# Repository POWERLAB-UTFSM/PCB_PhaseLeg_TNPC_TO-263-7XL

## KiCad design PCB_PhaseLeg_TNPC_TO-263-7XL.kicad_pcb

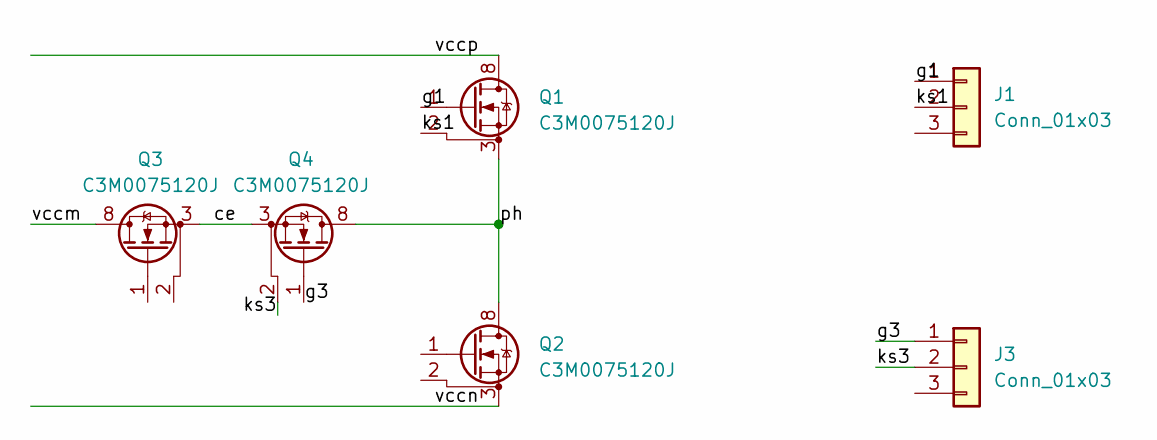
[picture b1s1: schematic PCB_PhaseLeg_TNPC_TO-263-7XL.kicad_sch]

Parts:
J1, J3: Conn_01x03; PinHeader_1x03_P1.27mm_Vertical_SMD_Pin1Left
Q1, Q2, Q3, Q4: C3M0075120J; TO-263-7_TabPin8

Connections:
/ce: Q3.3 (S), Q3.4 (S), Q3.5 (S), Q3.6 (S), Q3.7 (S), Q4.3 (S), Q4.4 (S), Q4.5 (S), Q4.6 (S), Q4.7 (S)
/g1: J1.1, Q1.1 (G)
/g3: J3.1, Q4.1 (G)
/ks1: J1.2, Q1.2 (DS)
/ks3: J3.2, Q4.2 (DS)
/ph: Q1.3 (S), Q1.4 (S), Q1.5 (S), Q1.6 (S), Q1.7 (S), Q2.8 (D), Q4.8 (D)
/vccm: Q3.8 (D)
/vccn: Q2.3 (S), Q2.4 (S), Q2.5 (S), Q2.6 (S), Q2.7 (S)
/vccp: Q1.8 (D)

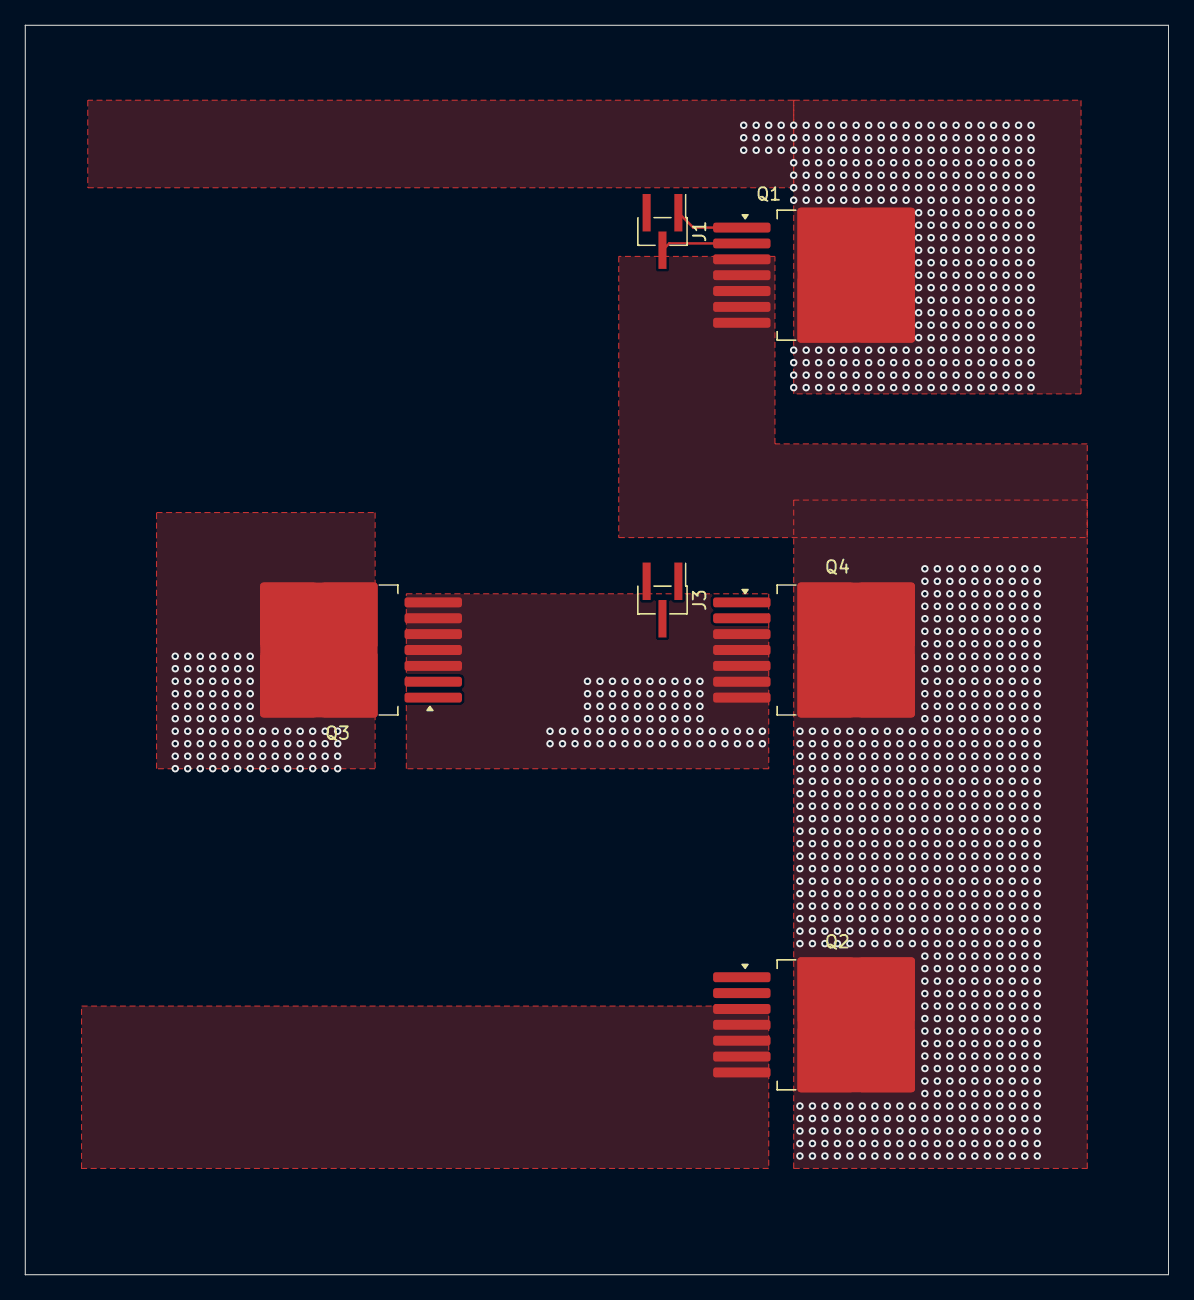
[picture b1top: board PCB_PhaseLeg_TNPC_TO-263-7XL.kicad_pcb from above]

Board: 2 copper layers, 91.5 x 100.0 mm, 6 parts (0 on the bottom side), 7 nets.

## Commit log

2024-06-06 pcb heatsink
